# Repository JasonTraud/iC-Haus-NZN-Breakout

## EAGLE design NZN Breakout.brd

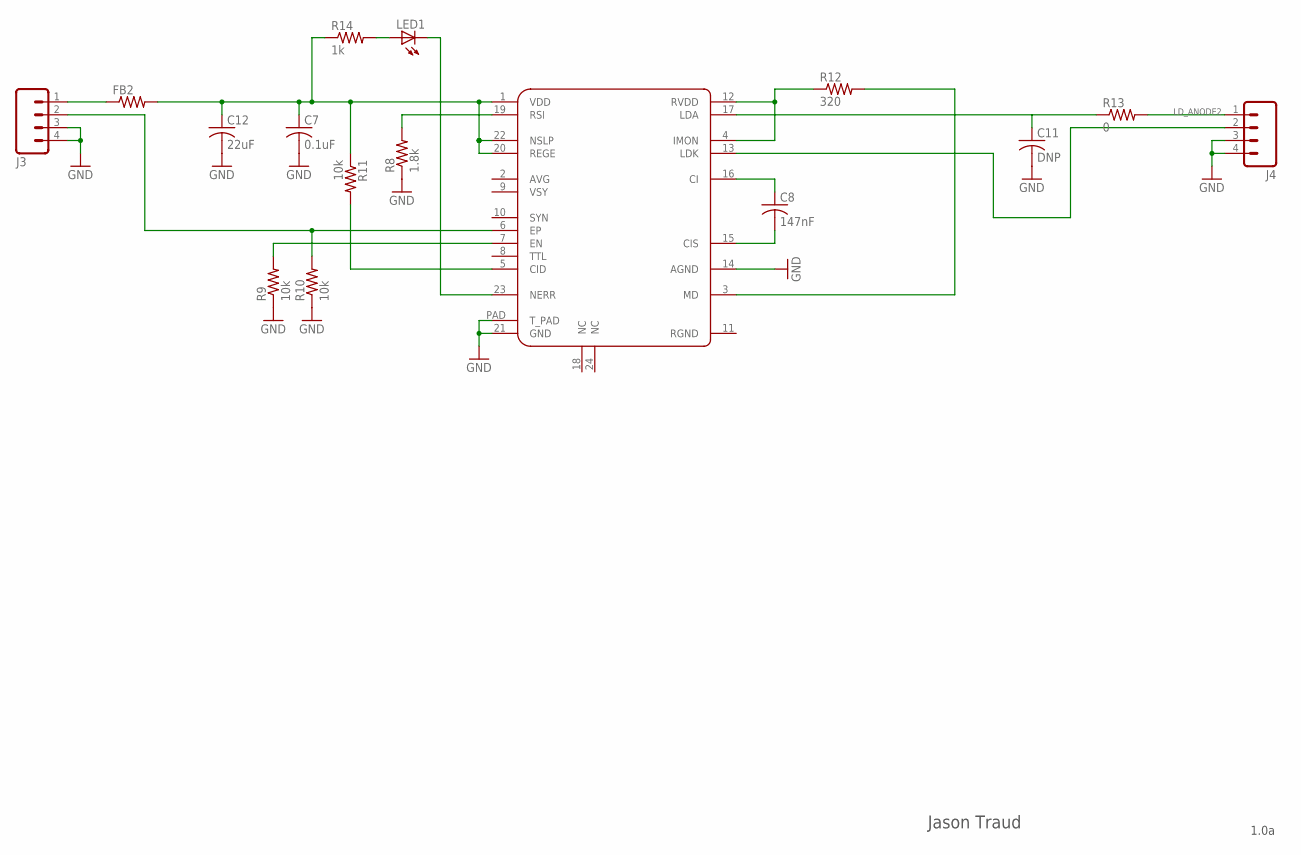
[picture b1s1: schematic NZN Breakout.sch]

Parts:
C7: 0.1uF; C0402
C8: 147nF; C0402
C11: DNP; C0805
C12: 22uF; C1206; MFG_PN TCTAL1C226M8R
FB2: R-US_R0805; R0805; MFG_PN MPZ2012S300A
J3, J4: 2X2; 2X2_1.27MM
LED1: LEDSML0805; SML0805
R8: 1.8k; R0402
R9, R10, R11: 10k; R0402
R12: 320; R0402
R13: 0; R0805
R14: 1k; R0402
U$1: IC-NZN; QFN24_PAD

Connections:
ENABLE_2: J3.2, R10.2, U$1.6 (EP)
GND: C7.2, C11.2, C12.2, J3.3, J3.4, J4.3, J4.4, R8.1, R9.1, R10.1, U$1.14 (AGND), U$1.21 (GND), U$1.PAD (T_PAD)
LD_ANODE2: J4.1, R13.2
unnamed: C8.1, U$1.16 (CI)
unnamed: R8.2, U$1.19 (RSI)
unnamed: R11.2, U$1.5 (CID)
unnamed: LED1.C, U$1.23 (NERR)
unnamed: J4.2, U$1.13 (LDK)
unnamed: C8.2, U$1.15 (CIS)
unnamed: R12.1, U$1.4 (IMON), U$1.12 (RVDD)
unnamed: R12.2, U$1.3 (MD)
unnamed: C11.1, R13.1, U$1.17 (LDA)
unnamed: FB2.1, J3.1
unnamed: LED1.A, R14.2
N_ENABLE_2: R9.2, U$1.7 (EN)
VIN2: C7.1, C12.1, FB2.2, R11.1, R14.1, U$1.1 (VDD), U$1.20 (REGE), U$1.22 (NSLP)

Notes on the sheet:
1.0a
Jason Traud

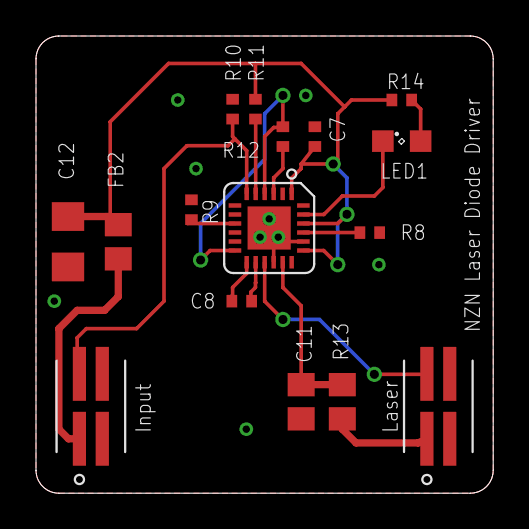
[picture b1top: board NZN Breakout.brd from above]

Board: 2 copper layers, 25.4 x 25.4 mm, 16 parts (0 on the bottom side), 16 nets.

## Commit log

2016-04-17 Initial Commit
    Initial commit of design and documentation

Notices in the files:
parts and their libraries:
SparkFun-Aesthetics: Licensing: Creative Commons ShareAlike 4.0 International - https://creativecommons.org/licenses/by-sa/4.0
frames: Released under the Creative Commons
Attribution Share-Alike 4.0 License
https://creativecommons.org/licenses/by-sa/4.0
